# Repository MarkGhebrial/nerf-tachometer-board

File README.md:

This is a PCB that simplifies the wiring of IR reflective sensors for use as tachometers in closed-loop brushed nerf flywheelers.

### Bill of materials:
 - Two [ITR20001-T sensors](https://www.adafruit.com/product/3930)
 - Two 470 ohm 1210 size resistors of your choosing (I chose [these](https://www.mouser.com/ProductDetail/Vishay-Dale/CRCW1210470RFKEA?qs=3R%2Fk7NrOSuXsW0BlMRX%252BmQ%3D%3D))
 - One [four-pin horizontal JST-PH connector](https://www.mouser.com/ProductDetail/JST-Commercial/S4B-PH-K-SLFSN?qs=QpmGXVUTftG04YaiaFwjFQ%3D%3D)

### Protean integration

I will publish the STEP files for the modified protean reviever cover once they have been printed and tested.

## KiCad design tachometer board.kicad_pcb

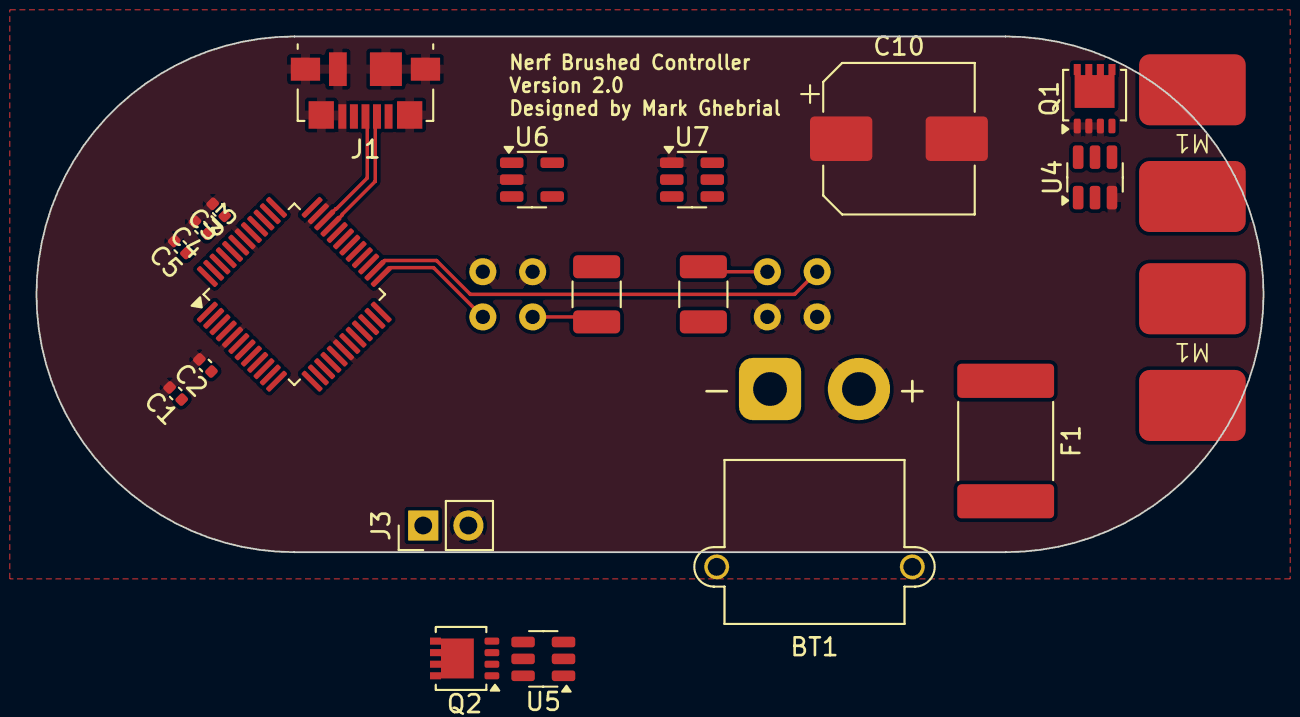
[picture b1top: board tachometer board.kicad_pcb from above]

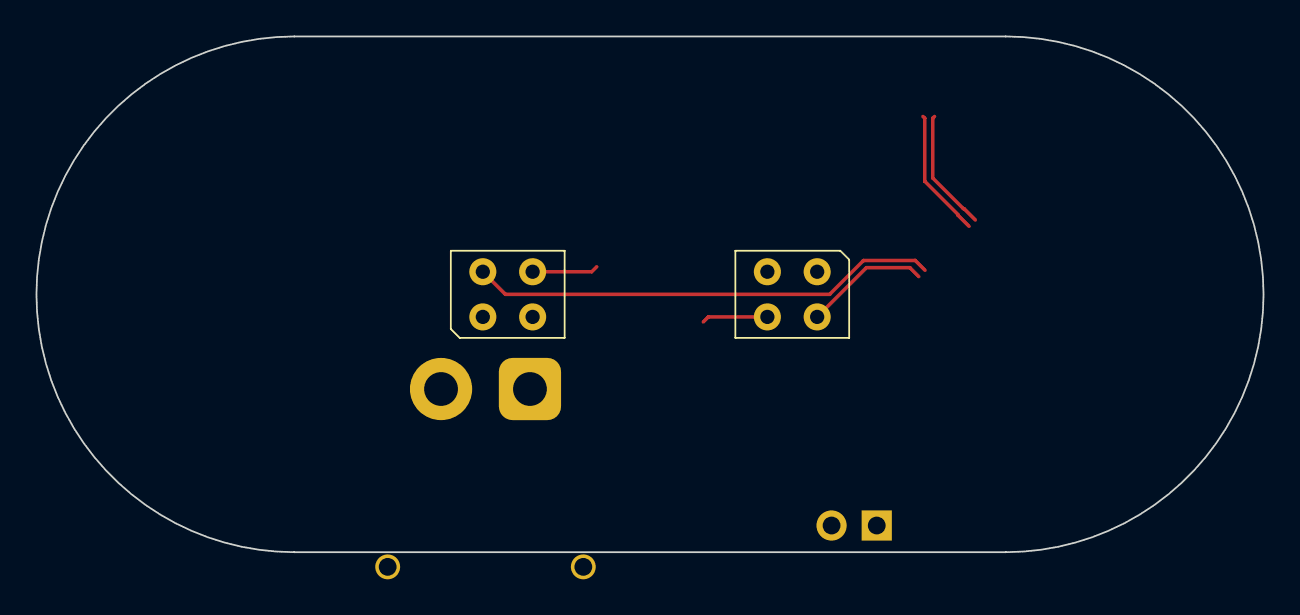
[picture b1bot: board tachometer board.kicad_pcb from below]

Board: 2 copper layers, 69.0 x 29.0 mm, 23 parts (2 on the bottom side), 15 nets.

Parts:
BT1: Battery; AMASS_XT30PW-M_1x02_P2.50mm_Horizontal
C1, C2, C3, C4: C; C_0402_1005Metric
C5: 1uF; C_0402_1005Metric
C10: 470uF; CP_Elec_8x10
F1: 5A; Fuse_2920_7451Metric
J1: USB_B_Micro; USB_Micro-B_Molex_47346-0001
J3: Conn_01x02_Pin; PinHeader_1x02_P2.54mm_Vertical
M1, M1#2: Motor_DC; 4mm_by_6mm_Solder_Pad_x2
Q1, Q2: PSMN8R5-40MSX; LFPAK33
R1, R2: 470; R_1210_3225Metric_Pad1.30x2.65mm_HandSolder
U1, U2: ITR20001-T
U3: ATSAMD21G18A-A; TQFP-48_7x7mm_P0.5mm
U4, U5: ZXGD3009DY; SOT-23-6
U6: AP2112K-3.3; SOT-23-5
U7: AP62250WU; TSOT-23-6

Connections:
+3.3V: R1.2, R2.2
+3V3: C1.1, C2.1, C3.1, C4.1, U3.6 (VDDANA), U3.17 (VDDIO), U3.36 (VDDIO), U3.44 (VDDIN), U6.5 (VOUT)
+BATT: F1.1, M1#2.1 (+), U4.1 (VCC), U5.1 (VCC), U7.3 (VIN), U7.5 (EN)
/GATEA: Q1.4 (G), U4.4 (SINK), U4.6 (SOURCE)
/GATEB: Q2.4 (G), U5.4 (SINK), U5.6 (SOURCE)
GND: BT1.2 (-), C1.2, C2.2, C3.2, C4.2, C5.2, C10.2, J1.5 (GND), J1.6 (Shield), J3.2, Q1.1 (S), Q1.2 (S), Q1.3 (S), Q2.1 (S), Q2.2 (S), Q2.3 (S), U1.1 (GND), U1.2 (GND), U2.1 (GND), U2.2 (GND), U3.5 (GNDANA), U3.18 (GND), U3.35 (GND), U3.42 (GND), U4.3 (GND), U5.3 (GND), U6.2 (GND), U7.1 (GND)
unnamed: BT1.1 (+), F1.2
unnamed: M1#2.2 (-), Q1.5 (D)
unnamed: R1.1, U1.3 (LED_VIN)
unnamed: R2.1, U2.3 (LED_VIN)
unnamed: C5.1, U3.43 (VDDCORE)
TACHA: U1.4 (Phototransistor_OUT), U3.26 (PA17)
TACHB: U2.4 (Phototransistor_OUT), U3.25 (PA16)
USB_D+: J1.3 (D+), U3.34 (PA25)
USB_D-: J1.2 (D-), U3.33 (PA24)

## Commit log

2025-01-02 Remove old files
2025-01-02 Remove lock files
2025-01-02 Remove .txt file extension from gitignore
2025-01-03 Update silkscreen and export gerbers
2025-01-03 Add README.md
2025-06-04 Add SAMD MCU and MOSFET
2025-09-24 Misc. changes to schematic and PCB
2025-09-24 Add buck converter
2025-10-01 Misc changes
2025-10-01 Update library
